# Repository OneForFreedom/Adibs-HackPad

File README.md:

# Adib's HackPad

(Before you critisise anything, its my first time - juuustttt.. keep that in mind please lol.)
I took 30 or more hours on this, trust me.
I did this over the course of a week.
started doing the tutorial 1:1, then I realised that you wern't meant to follow it.
so I salvaged what was useable, and completely pissed my parents by spending 6pm to 12am just doing it after school over the course of the previous week.
last thursday (26/06/25 dd/mm/yy) I messed up by saving old versons of my PCB files, which ruined the project. so I had to redo it.
Luckily I had pictures of the schematic which let me redo that pretty easily, and the pcb was the hard bit, but got it in about 7 hours after realising that I had saved sketches in my CAD editor (Fusion)
I went through all 5 stages of grief in 20 seconds

Btw it took me soo long because the concept of a PCB was alien to me.

Now since my sob story's done. lets get to the facts:

This is a 3x3 Key Matrix style MacoPad with a 0.91 inch I2C type oled (the highlight of the pain of my journey) and a rotary encoder for volume.

## The Main Hackpad!

## Schematic!

## The PCB

## The Case Parts

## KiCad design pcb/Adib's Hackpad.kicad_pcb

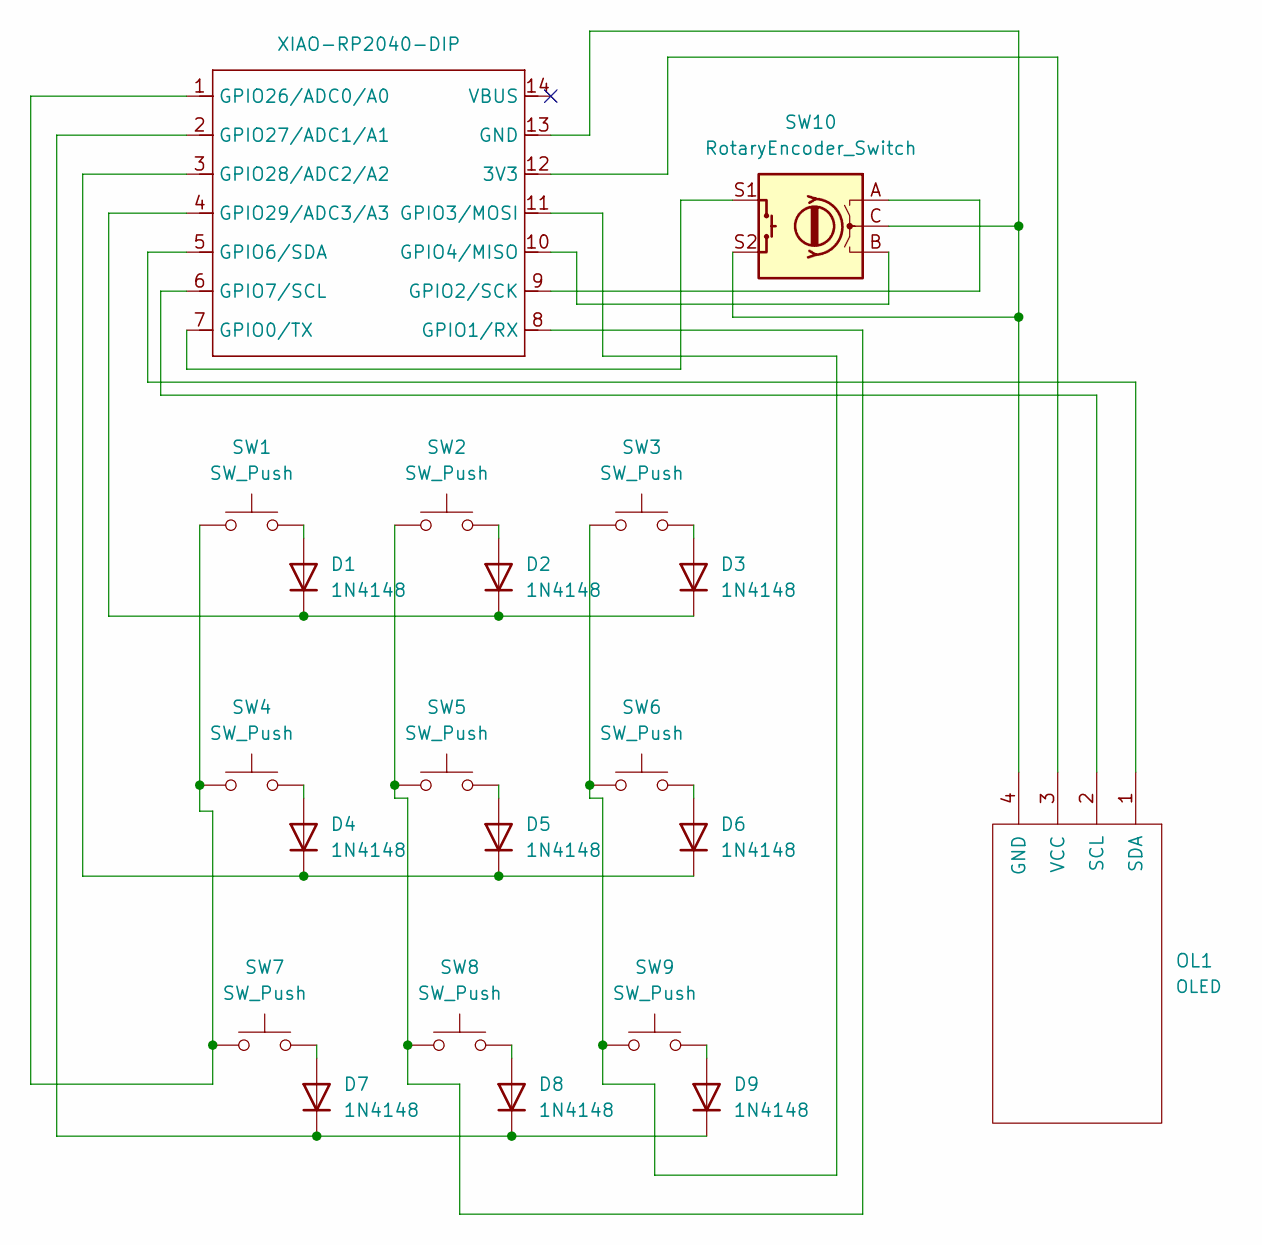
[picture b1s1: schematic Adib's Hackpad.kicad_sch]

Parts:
D1, D2, D3, D4, D5, D6, D7, D8, D9: 1N4148; D_DO-35_SOD27_P7.62mm_Horizontal
OL1: OLED; SSD1306-0.91-OLED-4pin-128x32
SW1, SW2, SW3, SW4, SW5, SW6, SW7, SW8, SW9: SW_Push; SW_Cherry_MX_1.00u_PCB
SW10: RotaryEncoder_Switch; RotaryEncoder_Alps_EC11E-Switch_Vertical_H20mm_CircularMoun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
U1: XIAO-RP2040-DIP

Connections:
unnamed: D1.2 (A), SW1.2
unnamed: D1.1 (K), D2.1 (K), D3.1 (K), U1.4 (GPIO29/ADC3/A3)
unnamed: D2.2 (A), SW2.2
unnamed: D3.2 (A), SW3.2
unnamed: D4.2 (A), SW4.2
unnamed: D4.1 (K), D5.1 (K), D6.1 (K), U1.3 (GPIO28/ADC2/A2)
unnamed: D5.2 (A), SW5.2
unnamed: D6.2 (A), SW6.2
unnamed: D7.2 (A), SW7.2
unnamed: D7.1 (K), D8.1 (K), D9.1 (K), U1.2 (GPIO27/ADC1/A1)
unnamed: D8.2 (A), SW8.2
unnamed: D9.2 (A), SW9.2
unnamed: OL1.4 (GND), SW10.C, SW10.S2, U1.13 (GND)
unnamed: OL1.2 (SCL), U1.6 (GPIO7/SCL)
unnamed: OL1.1 (SDA), U1.5 (GPIO6/SDA)
unnamed: OL1.3 (VCC), U1.12 (3V3)
unnamed: SW10.S1, U1.7 (GPIO0/TX)
unnamed: SW2.1, SW5.1, SW8.1, U1.8 (GPIO1/RX)
unnamed: SW10.A, U1.9 (GPIO2/SCK)
unnamed: SW3.1, SW6.1, SW9.1, U1.11 (GPIO3/MOSI)
unnamed: SW10.B, U1.10 (GPIO4/MISO)
unnamed: SW1.1, SW4.1, SW7.1, U1.1 (GPIO26/ADC0/A0)

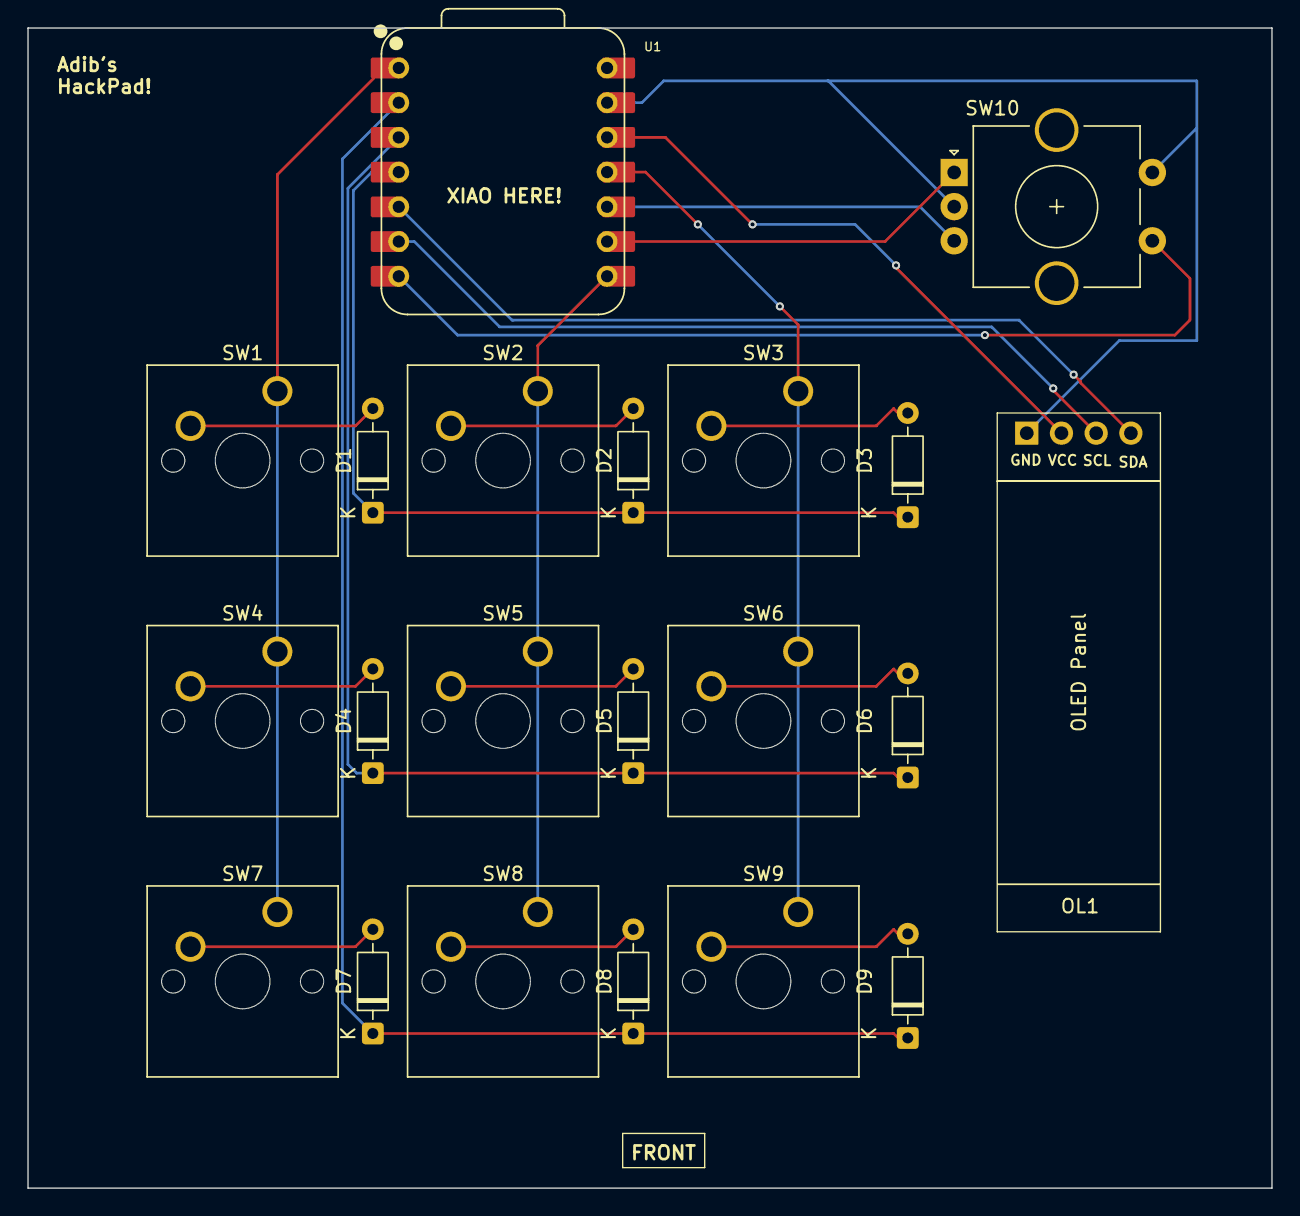
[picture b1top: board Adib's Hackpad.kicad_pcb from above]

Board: 2 copper layers, 91.0 x 84.9 mm, 21 parts (1 on the bottom side), 22 nets.

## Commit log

2025-08-06 Created using Colab
